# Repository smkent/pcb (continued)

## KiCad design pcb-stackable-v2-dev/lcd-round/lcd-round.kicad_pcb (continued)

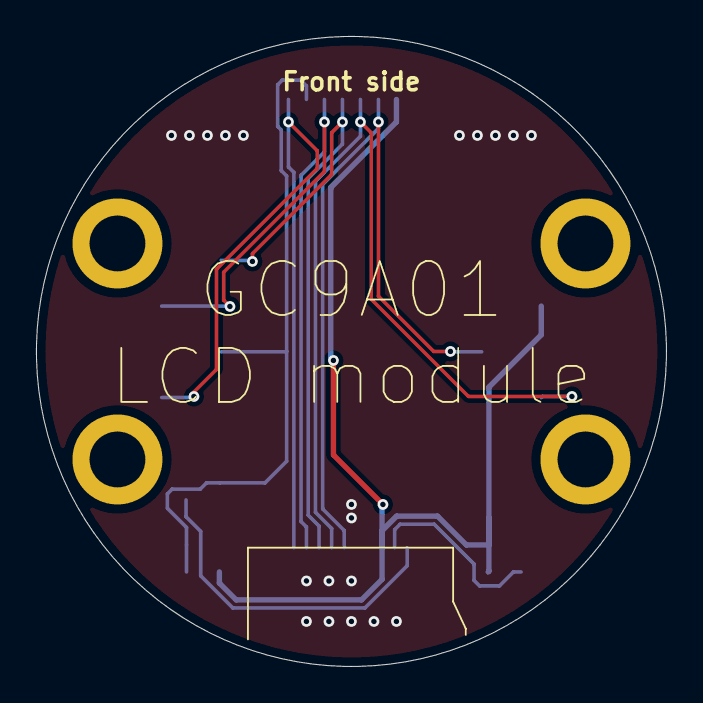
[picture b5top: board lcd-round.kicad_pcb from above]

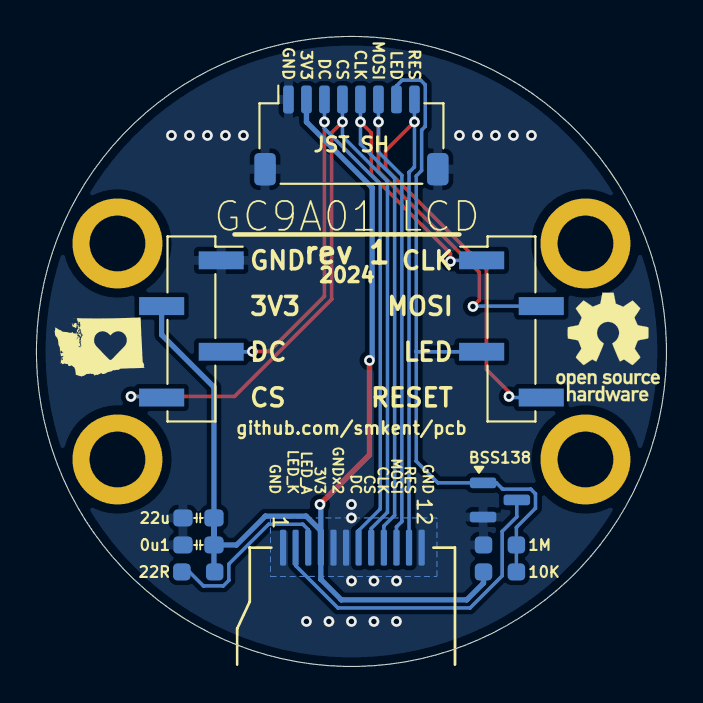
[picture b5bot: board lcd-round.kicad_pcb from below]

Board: 2 copper layers, 35.0 x 35.0 mm, 10 parts (10 on the bottom side), 10 nets.

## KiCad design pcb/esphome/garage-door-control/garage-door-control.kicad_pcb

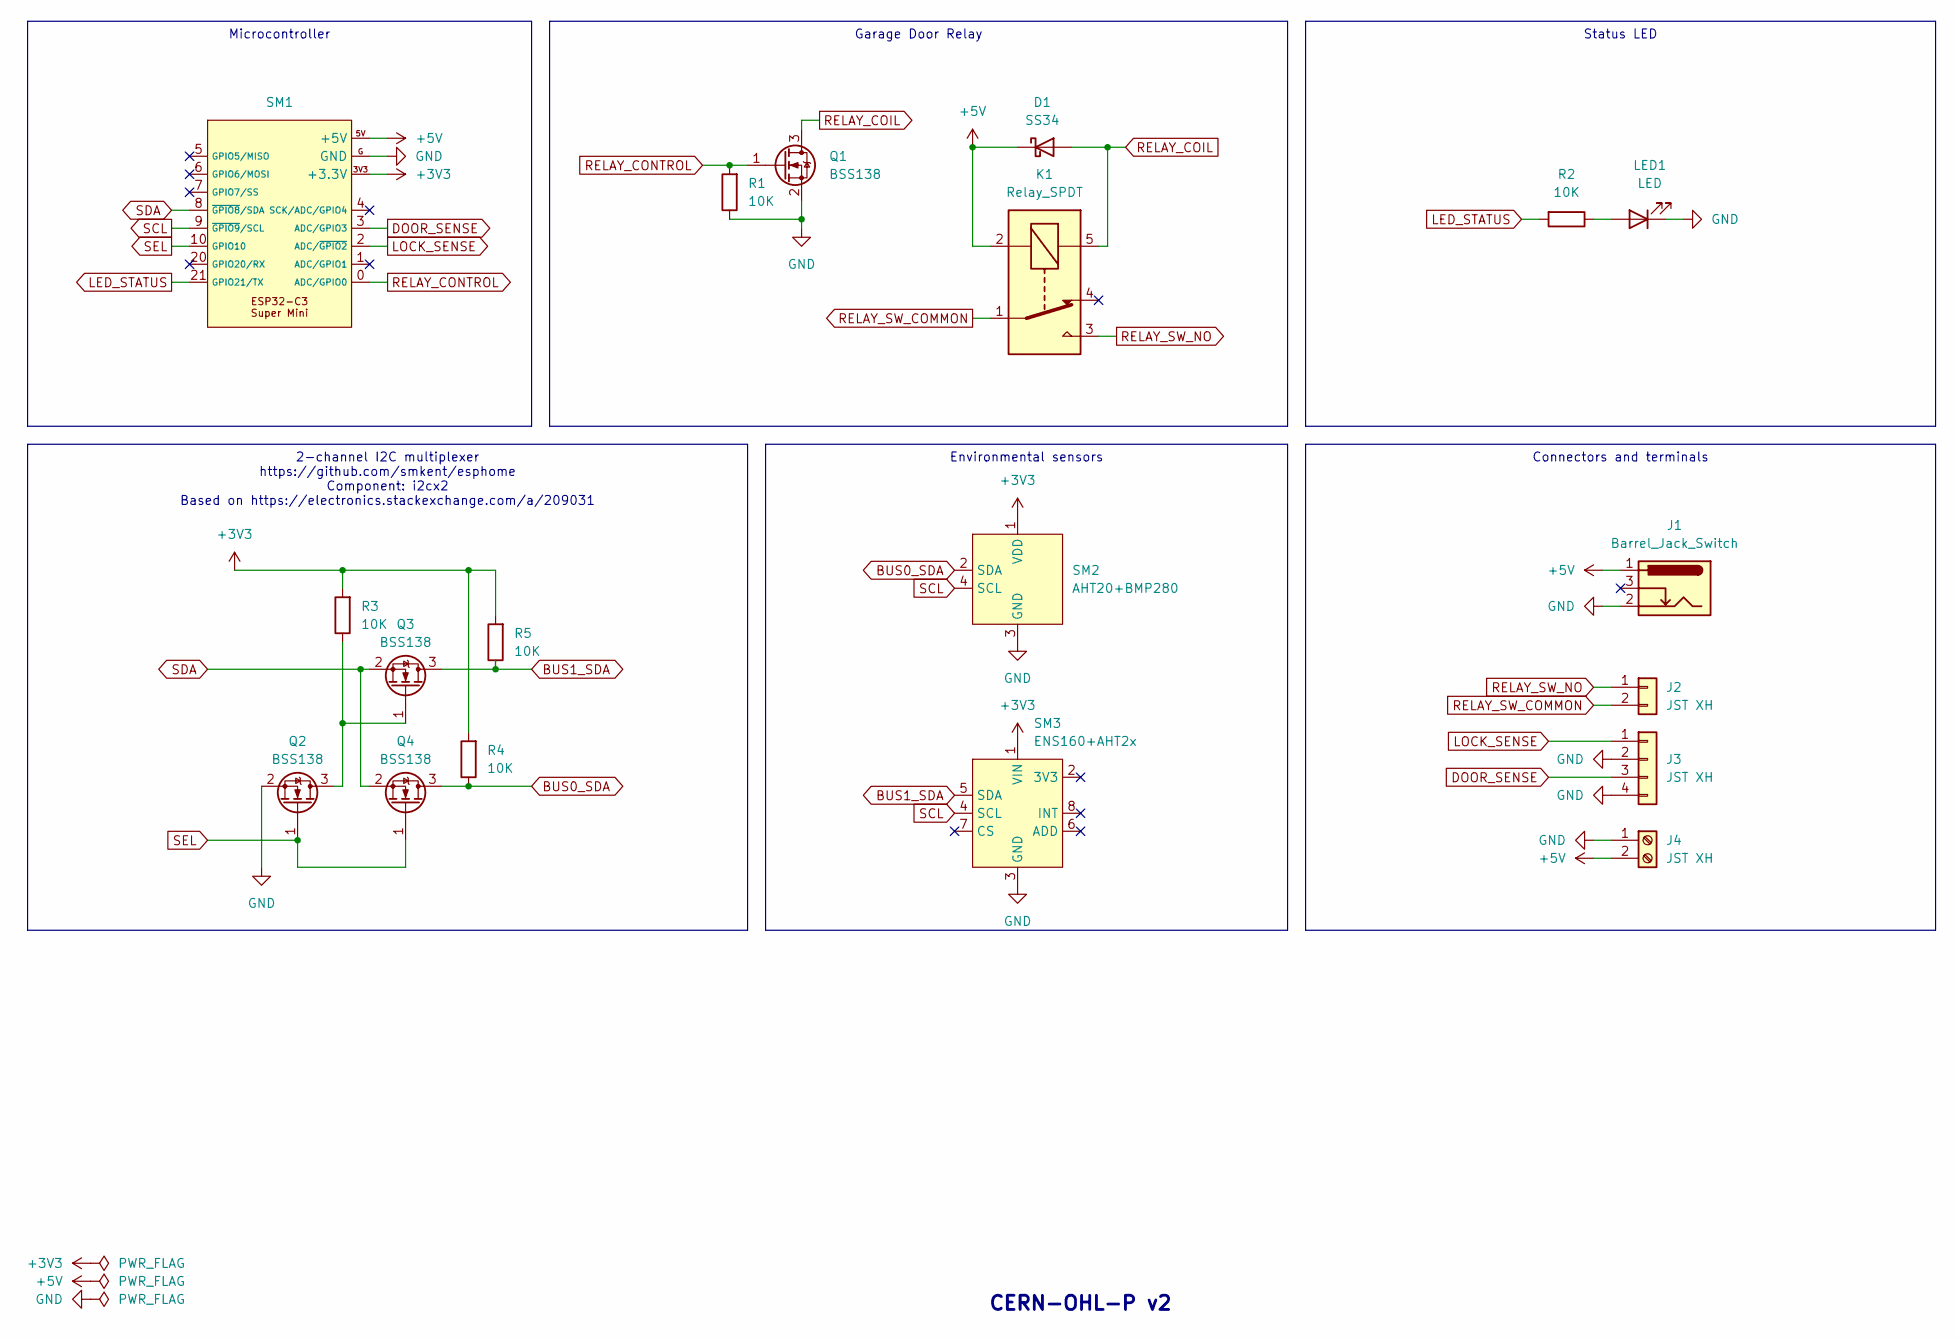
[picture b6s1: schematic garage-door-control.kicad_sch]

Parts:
D1: SS34; D_SMA
J1: Barrel_Jack_Switch; BarrelJack_DC-050_SMT_Horizontal
J2: JST XH; JST_XH_B2B-XH-A_1x02_P2.50mm_Vertical
J3: JST XH; JST_XH_B4B-XH-A_1x04_P2.50mm_Vertical
J4: JST XH; TerminalBlock_Phoenix_MKDS-1,5-2-5.08_1x02_P5.08mm_Horizont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
K1: Relay_SPDT; Relay_SPDT_SANYOU_SRD_Series_Form_C
LED1: LED; LED_0805_2012Metric_Pad1.15x1.40mm_HandSolder_simple
Q1, Q2, Q3, Q4: BSS138; SOT-23
R1, R2, R3, R4, R5: 10K; R_0805_2012Metric_Pad1.20x1.40mm_HandSolder
SM1: ESP32-C3-Super-Mini-Pins
SM2: AHT20+BMP280; AHT20+BMP280-noholes
SM3: ENS160+AHT2x; ENS160+AHT2x-noholes

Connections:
+3V3: R3.2, R4.2, R5.2, SM1.3V3 (+3.3V), SM2.1 (VDD), SM3.1 (VIN)
+5V: D1.1 (K), J1.1, J4.2, K1.2, SM1.5V (+5V)
BUS0_SDA: Q4.3 (D), R4.1, SM2.2 (SDA)
BUS1_SDA: Q3.3 (D), R5.1, SM3.5 (SDA)
DOOR_SENSE: J3.3, SM1.3 (ADC/GPIO3)
GND: J1.2, J3.2, J3.4, J4.1, LED1.1 (K), Q1.2 (S), Q2.2 (S), R1.1, SM1.G (GND), SM2.3 (GND), SM3.3 (GND)
LED_STATUS: R2.2, SM1.21 (GPIO21/TX)
LOCK_SENSE: J3.1, SM1.2 (ADC/~GPIO2)
unnamed: LED1.2 (A), R2.1
unnamed: Q2.3 (D), Q3.1 (G), R3.1
RELAY_COIL: D1.2 (A), K1.5, Q1.3 (D)
RELAY_CONTROL: Q1.1 (G), R1.2, SM1.0 (ADC/GPIO0)
RELAY_SW_COMMON: J2.2, K1.1
RELAY_SW_NO: J2.1, K1.3
SCL: SM1.9 (~GPIO9/SCL), SM2.4 (SCL), SM3.4 (SCL)
SDA: Q3.2 (S), Q4.2 (S), SM1.8 (~GPIO8/SDA)
SEL: Q2.1 (G), Q4.1 (G), SM1.10 (GPIO10)

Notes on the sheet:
Garage Door Relay
2-channel I2C multiplexer https://github.com/smkent/esphome Component: i2cx2 Based on https://electronics.stackexchange.com/a/209031
Environmental sensors
Microcontroller
Status LED
Connectors and terminals
CERN-OHL-P v2

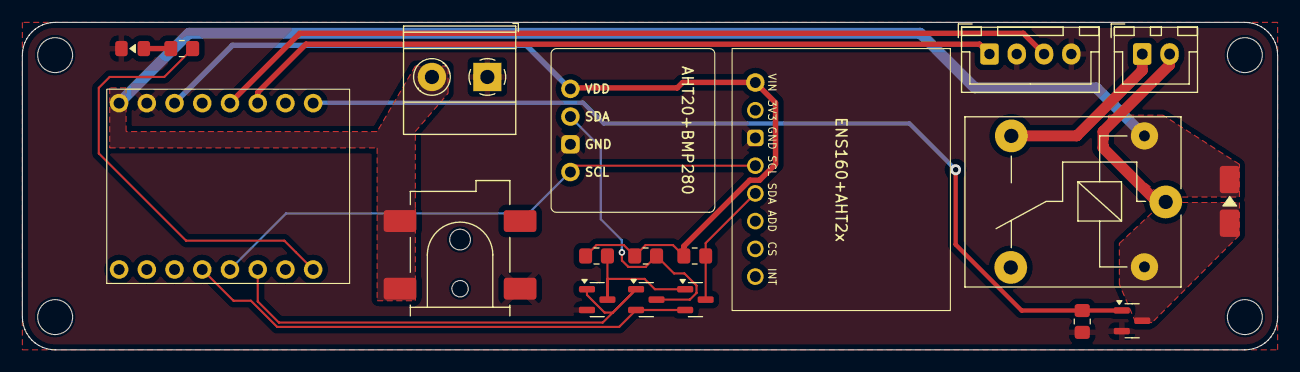
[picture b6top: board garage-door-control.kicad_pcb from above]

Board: 2 copper layers, 115.0 x 30.0 mm, 19 parts (0 on the bottom side), 17 nets.

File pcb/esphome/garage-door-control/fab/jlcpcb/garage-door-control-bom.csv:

Comment,Designator,Footprint,LCSC
LED,LED1,custom:LED_0805_2012Metric_Pad1.15x1.40mm_HandSolder_simple,
JST XH,J2,Connector_JST:JST_XH_B2B-XH-A_1x02_P2.50mm_Vertical,
Barrel_Jack_Switch,J1,Connector_BarrelJack:BarrelJack_CLIFF_FC681465S_SMT_Horizontal,
10K,"R1,R2,R3,R4,R5",Resistor_SMD:R_0805_2012Metric_Pad1.20x1.40mm_HandSolder,
JST XH,J3,Connector_JST:JST_XH_B4B-XH-A_1x04_P2.50mm_Vertical,
JST XH,J4,"custom:TerminalBlock_Phoenix_MKDS-1,5-2-5.08_1x02_P5.08mm_Horizontal",
BSS138,"Q1,Q2,Q3,Q4",Package_TO_SOT_SMD:SOT-23,
SS34,D1,custom:D_SMA_simple,
~,SM1,modules:ESP32-C3-Super-Mini-Pins,
~,SM2,modules:AHT20+BMP280-noholes,
Relay_SPDT,K1,Relay_THT:Relay_SPDT_SANYOU_SRD_Series_Form_C,
~,SM3,modules:ENS160+AHT2x-noholes,

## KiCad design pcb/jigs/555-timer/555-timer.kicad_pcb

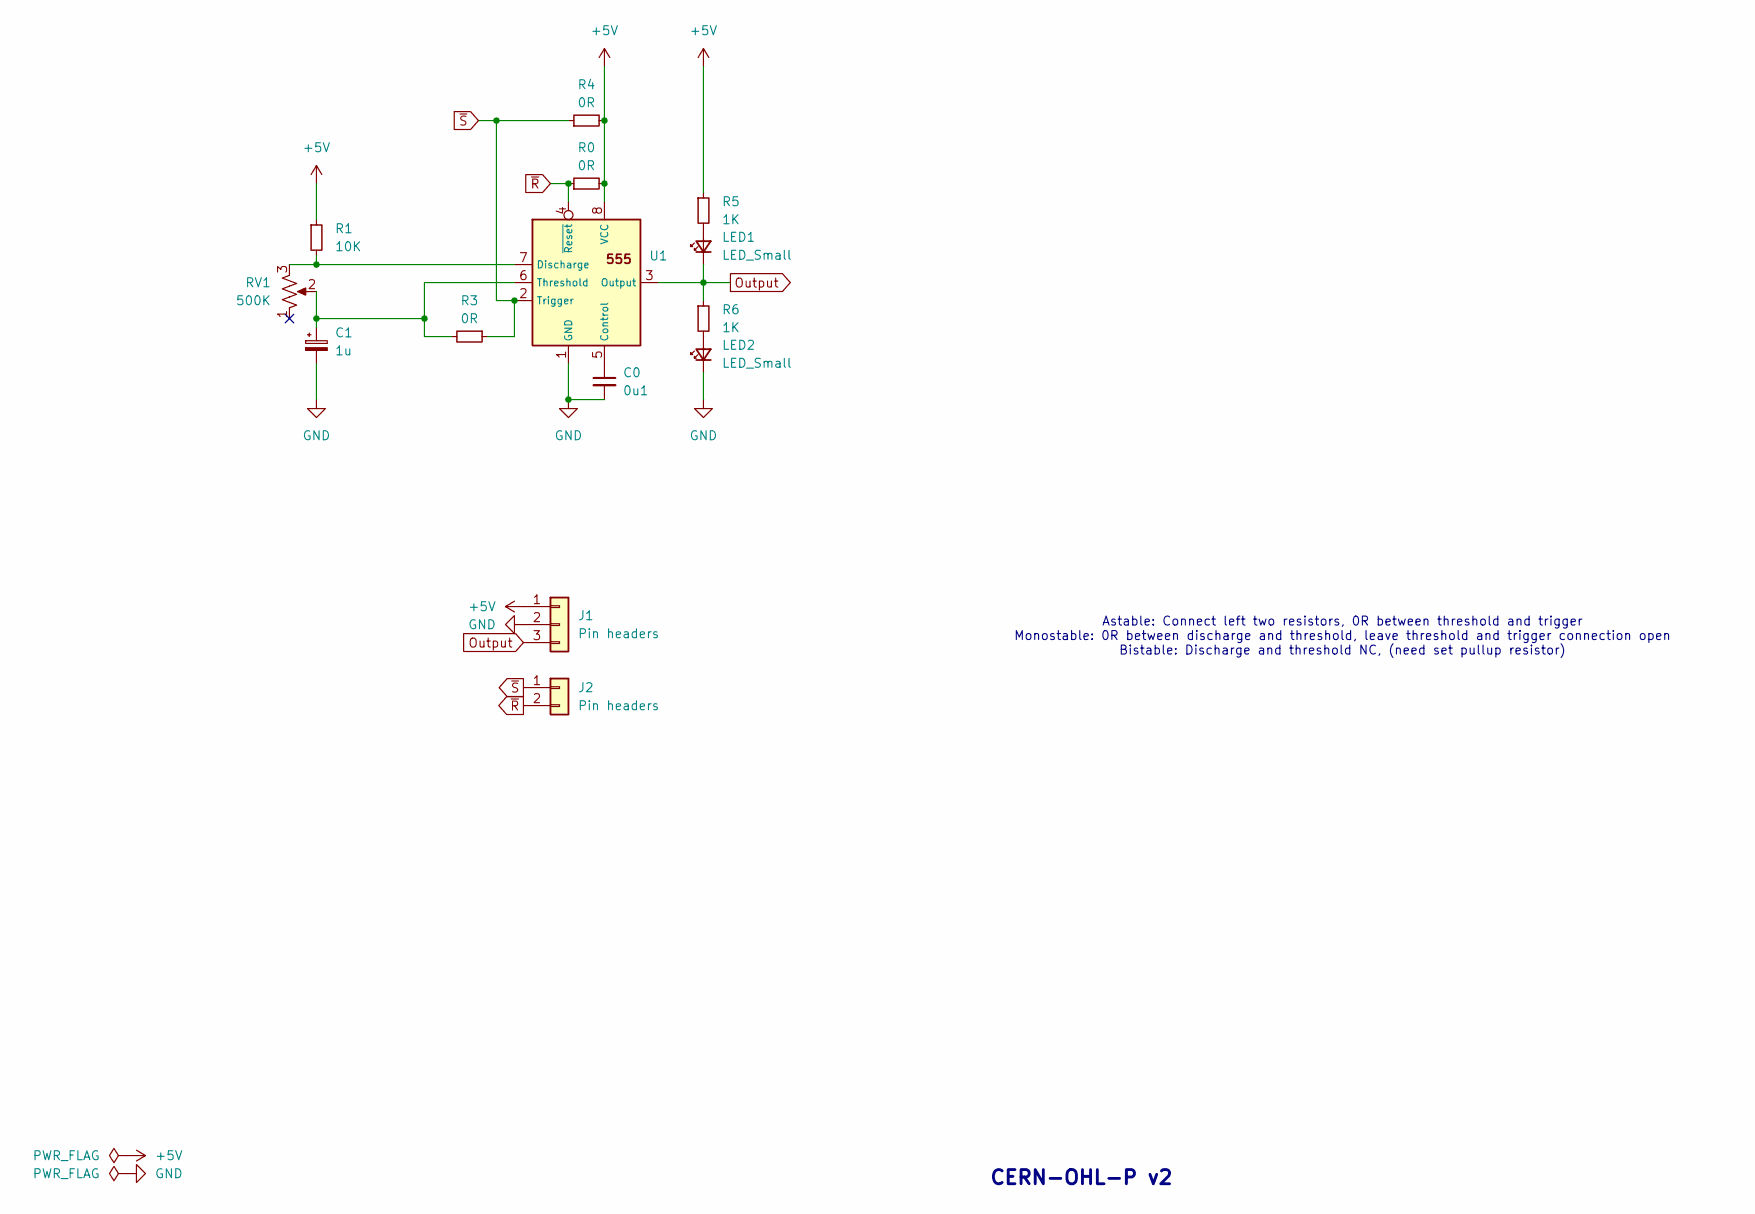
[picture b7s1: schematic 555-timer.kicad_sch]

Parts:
C0: 0u1; C_0603_1608Metric_Pad1.08x0.95mm_HandSolder
C1: 1u; C_Combo_CP_Elec_5x5.4
J1: Pin headers; PinHeader_1x03_P2.54mm_Vertical_simple_pad2gnd
J2: Pin headers; PinHeader_1x02_P2.54mm_Vertical_simple
LED1, LED2: LED_Small; LED_0603_1608Metric_Pad1.05x0.95mm_HandSolder_simple
R0, R3, R4: 0R; R_0603_1608Metric_Pad0.98x0.95mm_HandSolder
R1: 10K; R_0603_1608Metric_Pad0.98x0.95mm_HandSolder
R5, R6: 1K; R_0603_1608Metric_Pad0.98x0.95mm_HandSolder
RV1: 500K; Potentiometer_3.8mmx3.0mm_Vertical
U1: NE555; SOIC-8_3.9x4.9mm_P1.27mm

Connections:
+5V: J1.1, R0.2, R1.1, R4.2, R5.1, U1.8 (VCC)
GND: C0.2, C1.2, J1.2, LED2.1 (K), U1.1 (GND)
unnamed: LED1.2 (A), R5.2
unnamed: LED2.2 (A), R6.2
unnamed: C0.1, U1.5 (Control)
unnamed: R1.2, RV1.3, U1.7 (Discharge)
unnamed: C1.1, R3.2, RV1.2, U1.6 (Threshold)
Output: J1.3, LED1.1 (K), R6.1, U1.3 (Output)
~R: J2.2, R0.1, U1.4 (~Reset)
~S: J2.1, R3.1, R4.1, U1.2 (Trigger)

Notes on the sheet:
CERN-OHL-P v2
Astable: Connect left two resistors, 0R between threshold and trigger Monostable: 0R between discharge and threshold, leave threshold and trigger connection open Bistable: Discharge and threshold NC, (need set pullup resistor)

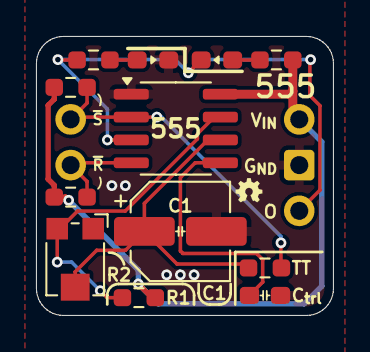
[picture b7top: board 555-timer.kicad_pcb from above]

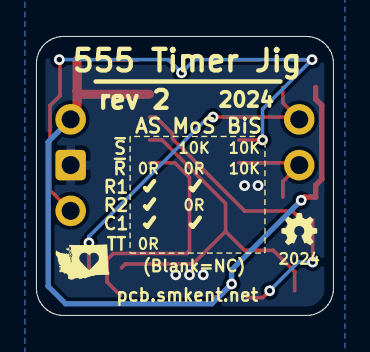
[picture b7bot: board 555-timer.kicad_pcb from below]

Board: 2 copper layers, 16.5 x 15.5 mm, 14 parts (2 on the bottom side), 10 nets.

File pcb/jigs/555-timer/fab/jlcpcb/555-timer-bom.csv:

Comment,Designator,Footprint,LCSC
0R,"R0,R3,R4",custom:R_0603_1608Metric_Pad0.98x0.95mm_HandSolder_simple,
500K,RV1,lcsc:RES-ADJ-SMD_VG039NCH,
0u1,C0,custom:C_0603_1608Metric_Pad1.08x0.95mm_HandSolder,
Pin headers,J2,custom:PinHeader_1x02_P2.54mm_Vertical_simple,
LED_Small,"LED1,LED2",custom:LED_0603_1608Metric_Pad1.05x0.95mm_HandSolder_simple,
1K,"R5,R6",custom:R_0603_1608Metric_Pad0.98x0.95mm_HandSolder_simple,
1u,C1,custom:C_Combo_CP_Elec_5x5.4,
Pin headers,J1,custom:PinHeader_1x03_P2.54mm_Vertical_simple_pad2gnd,
10K,R1,custom:R_0603_1608Metric_Pad0.98x0.95mm_HandSolder_simple,
NE555,U1,Package_SO:SOIC-8_3.9x4.9mm_P1.27mm,

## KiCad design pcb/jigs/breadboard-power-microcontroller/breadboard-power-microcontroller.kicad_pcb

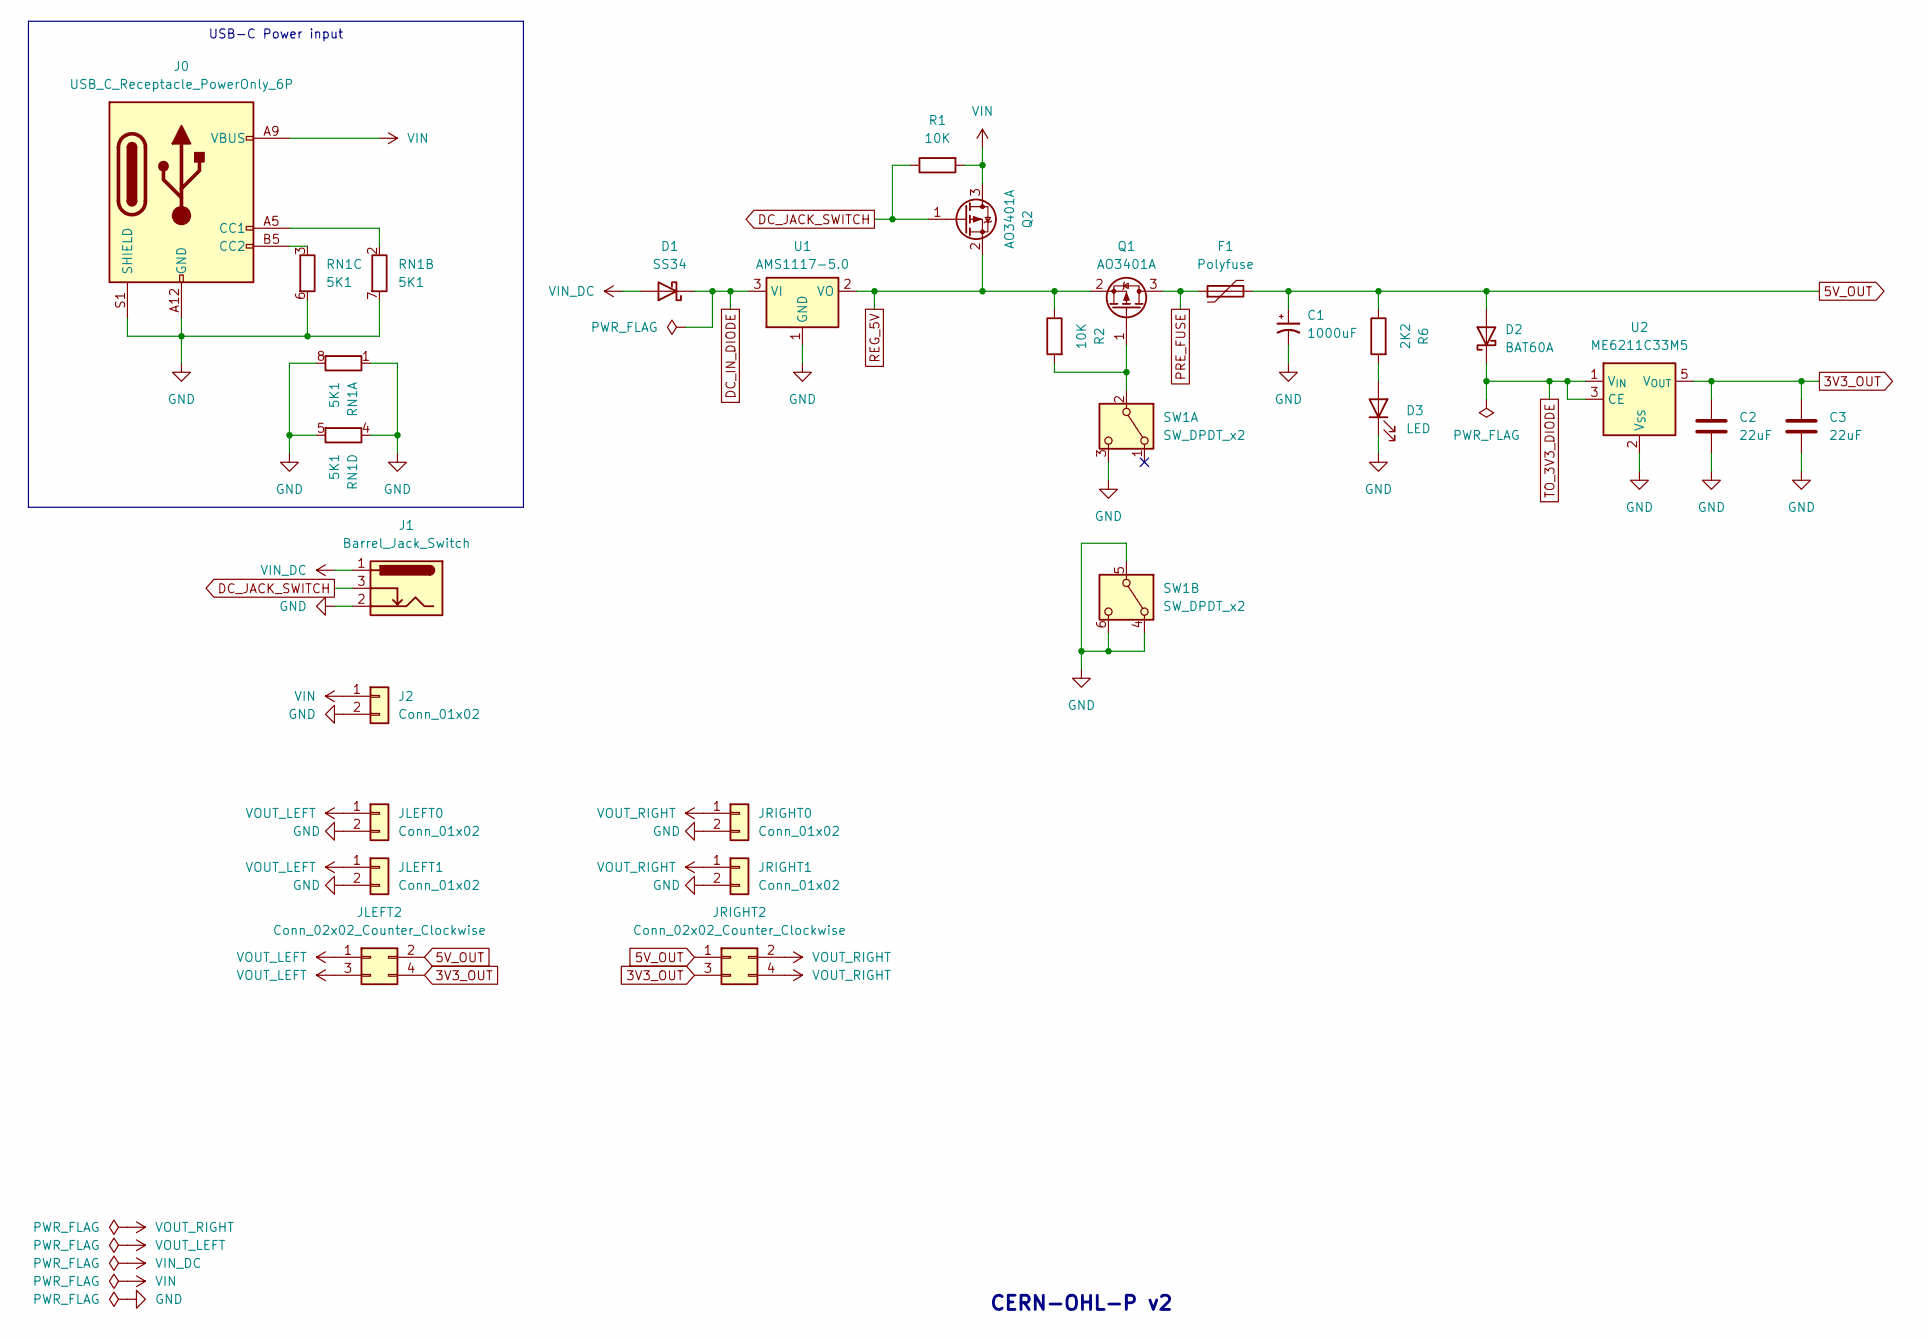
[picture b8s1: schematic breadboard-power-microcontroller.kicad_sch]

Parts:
C1: 1000uF; CP_Elec_8x10.5
C2, C3: 22uF; C_0805_2012Metric_Pad1.18x1.45mm_HandSolder
D1: SS34; D_SMA
D2: BAT60A; D_SOD-323_HandSoldering
D3: LED; LED_0805_2012Metric_Pad1.15x1.40mm_HandSolder_simple
F1: Polyfuse; Fuse_1206_3216Metric
J0: USB_C_Receptacle_PowerOnly_6P; USB_C_Receptacle_GCT_USB4125-xx-x_6P_TopMnt_Horizontal_Hand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
J1: Barrel_Jack_Switch; BarrelJack_DC-050_SMT_Horizontal
J2: Conn_01x02; JST_XH_S2B-XH-2AW_1x02_P2.50mm_TH-or-SMD_pad2gnd_trim
JLEFT0, JLEFT1: Conn_01x02; PinHeader_1x02_P2.54mm_Vertical_simple_pad2gnd
JLEFT2: Conn_02x02_Counter_Clockwise; PinHeader_2x02_P2.54mm_Vertical_simple
JRIGHT0, JRIGHT1: Conn_01x02; PinHeader_1x02_P2.54mm_Vertical_simple_pad2gnd
JRIGHT2: Conn_02x02_Counter_Clockwise; PinHeader_2x02_P2.54mm_Vertical_simple
Q1, Q2: AO3401A; SOT-23; LCSC Part C15127
R1, R2: 10K; R_0805_2012Metric_Pad1.20x1.40mm_HandSolder
R6: 2K2; R_0805_2012Metric_Pad1.20x1.40mm_HandSolder
RN1: 5K1; R_Array_Convex_4x0603
SW1: SW_DPDT_x2; SW_Push_DPDT_Toggle_7.0x7.0mm_THT
U1: AMS1117-5.0; SOT-223-3_TabPin2
U2: ME6211C33M5; SOT-23-5

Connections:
3V3_OUT: C2.1, C3.1, JLEFT2.4, JRIGHT2.3, U2.5 (V_{OUT})
5V_OUT: C1.1, D2.2 (A), F1.2, JLEFT2.2, JRIGHT2.1, R6.1
DC_IN_DIODE: D1.1 (K), U1.3 (VI)
DC_JACK_SWITCH: J1.3, Q2.1 (G), R1.1
GND: C1.2, C2.2, C3.2, D3.1 (K), J0.A12 (GND), J0.B12 (GND), J0.S1 (SHIELD), J1.2, J2.2, JLEFT0.2, JLEFT1.2, JRIGHT0.2, JRIGHT1.2, RN1.1 (R1.1), RN1.4 (R4.1), RN1.5 (R4.2), RN1.6 (R3.2), RN1.7 (R2.2), RN1.8 (R1.2), SW1.3 (C), SW1.4 (A), SW1.5 (B), SW1.6 (C), U1.1 (GND), U2.2 (V_{SS})
unnamed: D3.2 (A), R6.2
unnamed: J0.A5 (CC1), RN1.2 (R2.1)
unnamed: J0.B5 (CC2), RN1.3 (R3.1)
unnamed: Q1.1 (G), R2.2, SW1.2 (B)
PRE_FUSE: F1.1, Q1.3 (D)
REG_5V: Q1.2 (S), Q2.2 (S), R2.1, U1.2 (VO)
TO_3V3_DIODE: D2.1 (K), U2.1 (V_{IN}), U2.3 (CE)
VIN: J0.A9 (VBUS), J0.B9 (VBUS), J2.1, Q2.3 (D), R1.2
VIN_DC: D1.2 (A), J1.1
VOUT_LEFT: JLEFT0.1, JLEFT1.1, JLEFT2.1, JLEFT2.3
VOUT_RIGHT: JRIGHT0.1, JRIGHT1.1, JRIGHT2.2, JRIGHT2.4

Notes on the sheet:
USB-C Power input
CERN-OHL-P v2

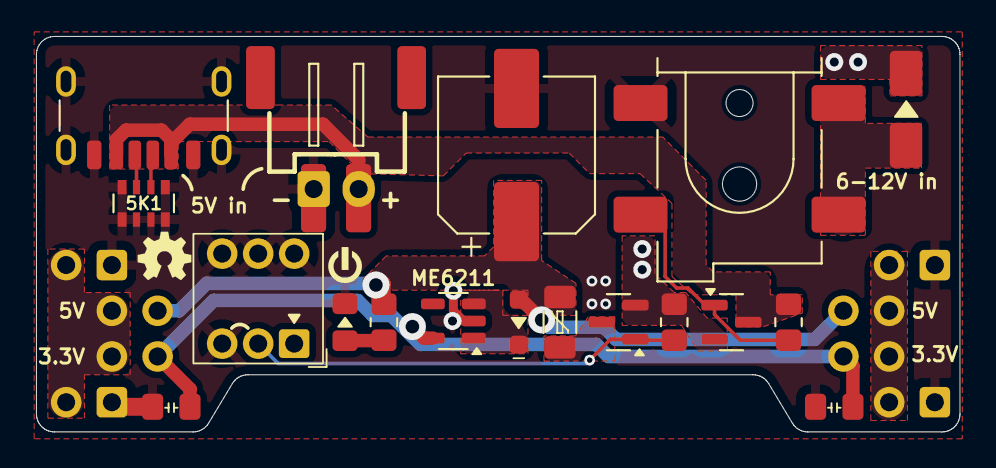
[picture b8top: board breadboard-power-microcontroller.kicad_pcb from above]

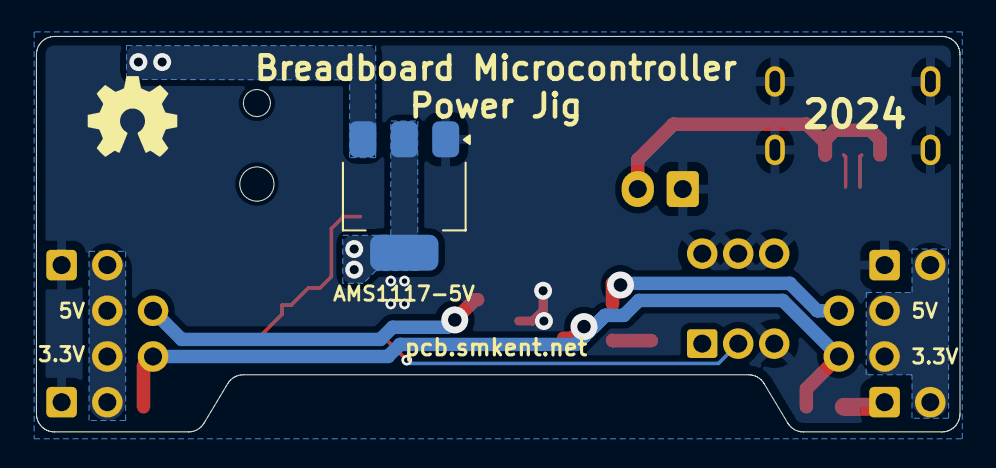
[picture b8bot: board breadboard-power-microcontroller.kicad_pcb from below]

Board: 2 copper layers, 51.3 x 22.0 mm, 25 parts (5 on the bottom side), 16 nets.

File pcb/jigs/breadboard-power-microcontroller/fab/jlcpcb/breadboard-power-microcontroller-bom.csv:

Comment,Designator,Footprint,LCSC
SW_DPDT_x2,SW1,lcsc:SW-TH_6P-L7.0-W7.0-P2.00_90deg,
Conn_02x02_Counter_Clockwise,"JLEFT2,JRIGHT2",custom:PinHeader_2x02_P2.54mm_Vertical_simple,
AO3401A,"Q1,Q2",Package_TO_SOT_SMD:SOT-23,C15127
Conn_01x02,"JLEFT0,JLEFT1,JRIGHT0,JRIGHT1",custom:PinHeader_1x02_P2.54mm_Vertical_simple_pad2gnd,
10K,"R1,R2",Resistor_SMD:R_0805_2012Metric_Pad1.20x1.40mm_HandSolder,
BAT60A,D2,custom:D_SOD-323_HandSoldering_simple,
1000uF,C1,Capacitor_SMD:CP_Elec_8x10.5,
Polyfuse,F1,custom:Fuse_1206_3216Metric_Pad1.42x1.75mm_HandSolder_simple,
22uF,"C2,C3",custom:C_0805_2012Metric_Pad1.18x1.45mm_HandSolder,
ME6211C33M5,U2,custom:SOT-23-5_HandSoldering_simple,
LED,D3,custom:LED_0805_2012Metric_Pad1.15x1.40mm_HandSolder_simple,
2K2,R6,Resistor_SMD:R_0805_2012Metric_Pad1.20x1.40mm_HandSolder,
AMS1117-5.0,U1,Package_TO_SOT_SMD:SOT-223-3_TabPin2,
USB_C_Receptacle_PowerOnly_6P,J0,custom:USB_C_Receptacle_GCT_USB4125-xx-x_6P_TopMnt_Horizontal_handsolder,
5K1,RN1,Resistor_SMD:R_Array_Convex_4x0603,
Conn_01x02,J2,custom:JST_XH_S2B-XH-2AW_1x02_P2.50mm_TH-or-SMD_pad2gnd_trim,
Barrel_Jack_Switch,J1,custom:DC-IN_DC-050-2.0-BB_rev2,
SS34,D1,custom:D_SMA_simple,
